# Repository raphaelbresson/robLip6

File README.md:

Ce projet est parytagé en 2 parties:<br/>
    -> <b>HIGH LEVEL</b> : Contient les dossiers contenant le code JAVA pour les actions de haut niveau (interface utilisateur)<br/>
	-> <b>HIGH LEVEL/Camera</b> : Contient le code de reconnaissance de couleur (pas de documentation)<br/>
	-> <b>HIGH LEVEL/RobLip6</b> : Contient les codes d'intégration (Pour l'instant juste la communication avec le LOW LEVEL)<br/>
	-> <b>HIGH LEVEL/roblip6</b> : Contient la javadoc des codes d'intégration<br/>
	-> <b>HIGH_LEVEL/JAVA_TCP</b> : Contient les codes de communication ethernet (ancienne version avec le microcontroleur MBED)<br/>
	-> LOW LEVEL : code VHDL destiné à la carte MOJO V3 (gestion des capteurs)<br/>
    -> <b>LOW_LEVEL/firmware_IMU</b> : Contient le code arduino du firmware de l'IMU (modification nécessaire pour récupérer directement des quaternions à la place des angles d'Euler).<br/>
	-> <b>FPGA</b> : Contient le code (VHDL) nécessaire pour programmer le FPGA (Carte MOJO dans notre cas)<br/>
	-> <b>MBED</b> : Contient le code (C++) nécessaire pour programmer le microcontroleur MBED (plan B) <br/>
	-> <b>RobLip6</b> : Contient le design (EAGLE) du circuit imprimé pour la solution FPGA <br/>
Les scripts shells ("<b>config2octets.sh</b>" et "<b>config4octets.sh</b>" placés à la racine permettant de revenir à une configuration 2 bits (respectivement 4 bits).<br/>
Bonne lecture!

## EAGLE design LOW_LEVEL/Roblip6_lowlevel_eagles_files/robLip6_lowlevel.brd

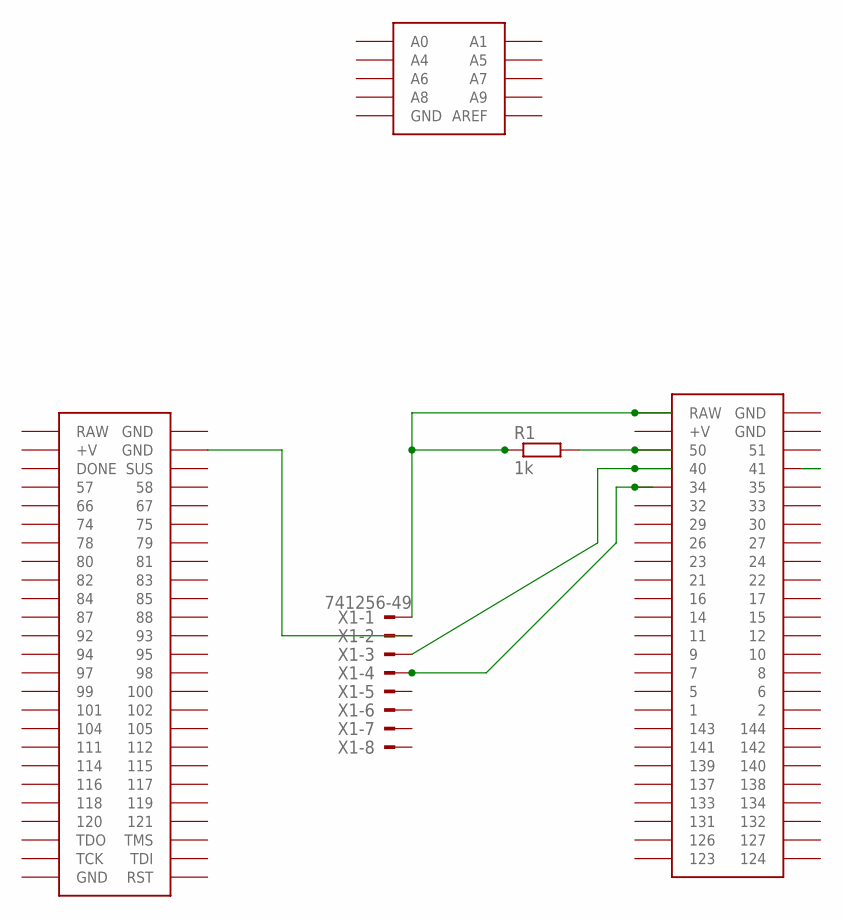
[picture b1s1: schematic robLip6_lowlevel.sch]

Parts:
R1: 1k; 0207/10
U$1: MOJOV3; MOJO_V3
X1: 741256-49

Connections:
GND@2: U$1.GND@4 (GND), X1.2
unnamed: R1.2, U$1.50
unnamed: U$1.40, X1.3
unnamed: U$1.34, X1.4
RAW: R1.1, U$1.RAW@1 (RAW), X1.1

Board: 2 copper layers, 3 parts (0 on the bottom side), 5 nets, no tracks yet.

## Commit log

2016-02-05 commit analyse fonctionnelle
2016-02-14 ajout de scenarios à la fiche de test et mise à jour des designs
2016-02-14 fiche de tests et designs
2016-02-19 Commit rapport
2016-02-19 Modification rapport projet
2016-02-20 ajout de l'analyse fonctionnelle dans le rapport de projet
2016-02-23 test lidar
2016-02-23 cahier de recette
2016-02-23 connexion de lidar et carte arduino uno
2016-02-26 modification trame TCP
2016-03-04 commit du design vhdl testant le bon fonctionnement des sorties pwm et des entrée analogIn (avec testbenchs)
2016-03-07 commit du design VHDL pwm, analogIn, I2C
2016-03-08 update PWM
2016-03-09 Communication des cartes
2016-03-22 Correction i2c et lidar non fonctionnelle pratiquement mais validable par simu
2016-03-22 ajout java uart
2016-03-22 correction I2C avec Mr Pecheux
2016-03-29 uart non fonctionnel: données reçues dans le désordre
2016-03-29 ajout d'un petitutilitaire de debug de l'interface uart en c
2016-03-29 camera
2016-04-04 Ajout LOW LEVEL fonctionnel sous MBED + update du code JAVA
2016-04-05 nettoyage
2016-04-05 update code vhdl
2016-05-02 Commit integration low level lidar + servos + roues
2016-05-16 final commit
2016-05-16 last commit
2016-05-17 commit PCB
2016-05-27 commit_readme
2016-05-27 commit_readme2
2016-05-27 commit_readme3_scripts_config
2016-06-08 commit oieces 3D lidar
